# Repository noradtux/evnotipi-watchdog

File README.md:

# Adafruit Trinket M0 watchdog for EVNotiPi
I shared this board on two manufacturers sites:
- https://aisler.net/p/TADOVIMT (shipping from Germany and USA; quicker but more expensive; also can source all parts for assembly by ordering "Precious Parts")
- https://oshpark.com/shared_projects/yOh5dQH3 (shipping from USA; slow)
See hardware/BOM.txt

## Building
You will need PlatformIO for building and installing the firmware. See https://docs.platformio.org/en/latest/installation.html for installation instructions.

To build and upload attach the Trinket M0 by USB and run ```pio run -t upload```.

# Easy adaptor for connecting the watchdog to the Pi
Plugging in patch cables in top of the CAN hat uses lots of space which the case does not provide. So the original solution was to bend the pins to save some verical space. Now there is a simple adaptor board which saves some millimeters and also allows connecting through a 5 pin ribbon cable.

Available here: https://aisler.net/p/ODQEXOXX

I suggest using a 10cm female-female jumper cable with (at least) 5 pins.

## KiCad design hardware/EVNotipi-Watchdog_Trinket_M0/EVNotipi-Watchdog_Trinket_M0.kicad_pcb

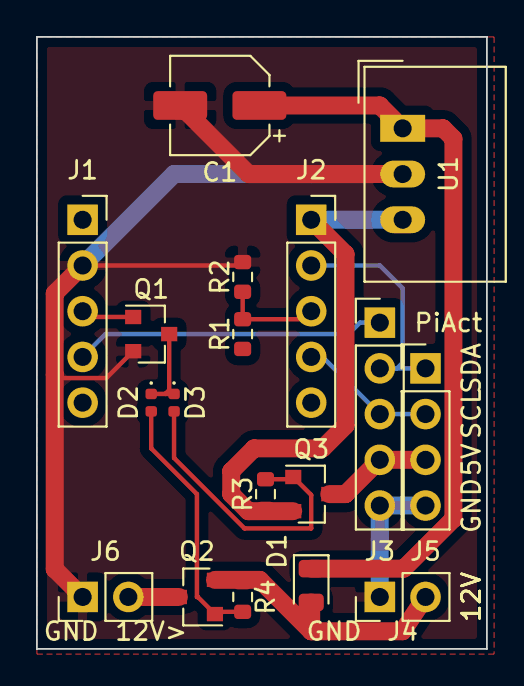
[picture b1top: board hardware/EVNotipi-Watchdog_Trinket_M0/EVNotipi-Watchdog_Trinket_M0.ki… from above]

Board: 2 copper layers, 25.0 x 34.0 mm, 18 parts (0 on the bottom side), 14 nets.

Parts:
C1: CP; CP_Elec_5x3
D1: D_Schottky; D_0805_2012Metric
D2, D3: D_Schottky; D_0402_1005Metric
J1: Conn_M0_Left; PinSocket_1x05_P2.54mm_Vertical
J2: Conn_M0_Right; PinSocket_1x05_P2.54mm_Vertical
J3: Conn_Pi; PinHeader_1x05_P2.54mm_Vertical
J4, J6: Conn_Pwr; PinHeader_1x02_P2.54mm_Vertical
J5: Conn_i2c; PinHeader_1x04_P2.54mm_Vertical
Q1: 2N7002; SOT-23
Q2, Q3: IRLML9301; SOT-23
R1: R100K; R_0603_1608Metric
R2, R3, R4: R27K; R_0603_1608Metric
U1: TSR_2-2450; Converter_DCDC_TRACO_TSR-1_THT

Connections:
5V_ENA: J1.3, Q1.1
12V_OUT: J6.2, Q2.3
ADC: J2.3, R1.2, R2.2
GND: C1.2, J1.2, J3.5, J4.1, J5.4, J6.1, Q1.2, R2.1, U1.2
unnamed: C1.1, D1.1, U1.1
unnamed: D2.1, D3.1, Q1.3
unnamed: D2.2, Q2.1, R4.1
unnamed: D3.2, Q3.1, R3.1
Pi_Running: J1.4, J3.1
SCL: J2.4, J3.3, J5.2
SDA: J2.2, J3.2, J5.1
VCC5V: J2.1, Q3.2, R3.2, U1.3
VCC12V: D1.2, J4.2, Q2.2, R1.1, R4.2
VCC_Pi: J3.4, J5.3, Q3.3

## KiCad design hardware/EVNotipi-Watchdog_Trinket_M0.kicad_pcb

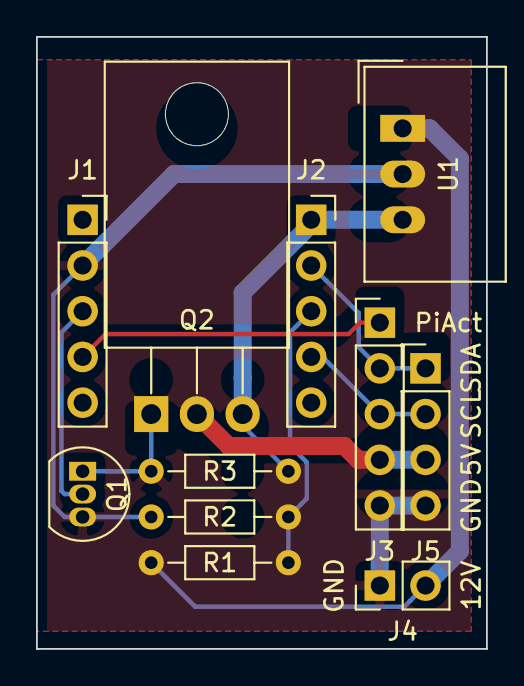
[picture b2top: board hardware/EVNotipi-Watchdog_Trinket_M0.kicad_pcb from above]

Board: 2 copper layers, 25.0 x 34.0 mm, 11 parts (0 on the bottom side), 10 nets.

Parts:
J1: Conn_Left; PinSocket_1x05_P2.54mm_Vertical
J2: Conn_Right; PinSocket_1x05_P2.54mm_Vertical
J3: Conn_Pi; PinHeader_1x05_P2.54mm_Vertical
J4: Conn_Pwr; PinHeader_1x02_P2.54mm_Vertical
J5: Conn_01x04_Male; PinHeader_1x04_P2.54mm_Vertical
Q1: BS170; TO-92_Inline
Q2: IRF5305; TO-220-3_Horizontal_TabDown
R1: R100K; R_Axial_DIN0204_L3.6mm_D1.6mm_P7.62mm_Horizontal
R2, R3: R27K; R_Axial_DIN0204_L3.6mm_D1.6mm_P7.62mm_Horizontal
U1: TSR_2-2450; Converter_DCDC_TRACO_TSR-1_THT

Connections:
5V_ENA: J1.3, Q1.2
ADC: J2.3, R1.2, R2.2
GND: J1.2, J3.5, J4.1, J5.4, Q1.3, R2.1, U1.2
unnamed: Q1.1, Q2.1, R3.1
Pi_Running: J1.4, J3.1
SCL: J2.4, J3.3, J5.2
SDA: J2.2, J3.2, J5.1
VCC5V: J2.1, Q2.3, R3.2, U1.3
VCC12V: J4.2, R1.1, U1.1
VCC_Pi: J3.4, J5.3, Q2.2

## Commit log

2019-07-07 Kevin's Version
2019-07-08 reindent
2019-07-12 adjust stile
2019-07-12 change scope
2019-07-14 add platform.io
2019-07-16 pio config
2019-07-23 works
2019-08-20 Try to improve ADC noise
2019-08-20 Power reduction
2019-08-27 port to M0 and Arduino
2019-09-03 improve i2c handling
2019-09-08 modify low voltage feedback
2019-09-08 implement a simple filter to reduce ADC noise
2019-09-18 add hardware design
2019-09-24 give the resistors and the TSR2-2450 more space
2019-10-01 Move some labels around
2019-10-01 Add README.md
2019-10-01 Beef up current carrying traces
2019-11-01 add BOM
2019-11-01 add M0 to BOM
2019-11-01 mention BOM in README
2019-11-22 add Raspi watchdog adapter
2019-11-22 move Trinket board to seperate directory
2019-11-22 Mention adapter board in README
2019-11-22 describe the cable needed
2019-12-25 Add buffer capacitor and a diode for backflow suppression and protection from polarity reversal
2019-12-25 Add labels to silk scren
2019-12-28 convert to uint-family of datatypes
2020-01-02 add some more debug code
2020-02-03 specify upload port
2020-02-04 fix GND plate
2020-04-15 add comments with pin numbers
2020-04-15 kicad...
2021-12-04 Wait 60 sesoncds after power on to allow rasPi to boot fully
2022-05-08 Update BOM.txt
    Add D1
2023-03-21 make emergency shutdown less sensitive. Wait 5 seconds.
2024-01-21 updates to board
2024-01-21 user serial/by-id for upload-port
2024-01-27 filter small glitches in running indicator
2024-04-10 use and pin current version of Time
